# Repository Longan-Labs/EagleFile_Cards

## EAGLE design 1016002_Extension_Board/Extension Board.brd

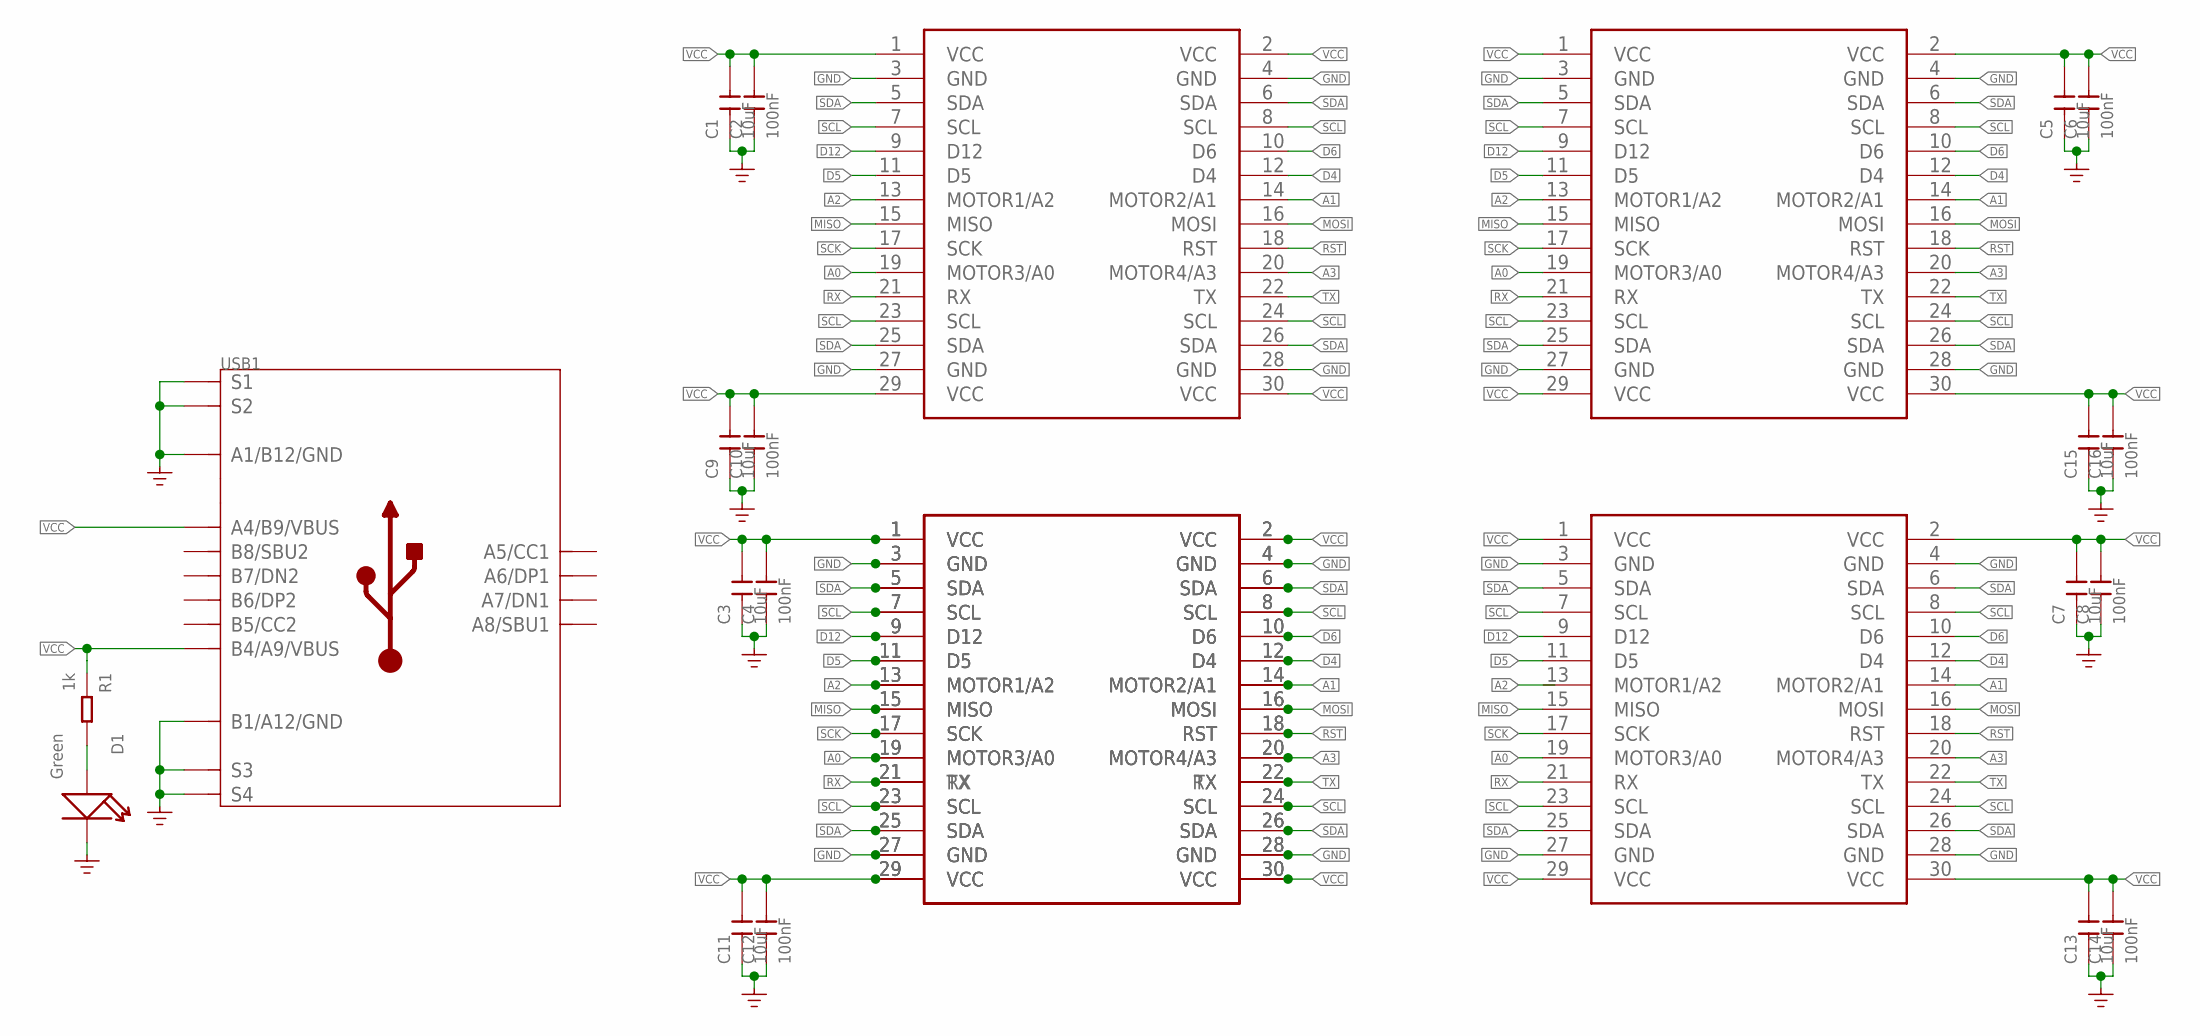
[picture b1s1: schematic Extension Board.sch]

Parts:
C1, C3, C5, C7, C9, C11, C13, C15: 10uF; C0603
C2, C4, C6, C8, C10, C12, C14, C16: 100nF; C0603
D1: Green; LED-0603
MOUDLE1, MOUDLE2, MOUDLE3: MOUDLE-2X15P-2.54'2.54'; 2X15P-2.54
MOUDLE4: MOUDLE-2X15P-2.54'90D'; 2X15P-2.54-90D
MOUDLE5: MOUDLE-2X15P-2.54-PAD'BOARD'; MOUDLE-2X15P-2.54
R1: 1k; R0603
USB1: USB2.0-TYPE-C

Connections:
A0: MOUDLE1.19 (MOTOR3/A0), MOUDLE2.19 (MOTOR3/A0), MOUDLE3.19 (MOTOR3/A0), MOUDLE4.19 (MOTOR3/A0), MOUDLE5.19 (MOTOR3/A0)
A1: MOUDLE1.14 (MOTOR2/A1), MOUDLE2.14 (MOTOR2/A1), MOUDLE3.14 (MOTOR2/A1), MOUDLE4.14 (MOTOR2/A1), MOUDLE5.14 (MOTOR2/A1)
A2: MOUDLE1.13 (MOTOR1/A2), MOUDLE2.13 (MOTOR1/A2), MOUDLE4.13 (MOTOR1/A2), MOUDLE5.13 (MOTOR1/A2)
A3: MOUDLE1.20 (MOTOR4/A3), MOUDLE2.20 (MOTOR4/A3), MOUDLE3.20 (MOTOR4/A3), MOUDLE4.20 (MOTOR4/A3), MOUDLE5.20 (MOTOR4/A3)
D4: MOUDLE1.12 (D4), MOUDLE2.12 (D4), MOUDLE3.12 (D4), MOUDLE4.12 (D4), MOUDLE5.12 (D4)
D5: MOUDLE1.11 (D5), MOUDLE2.11 (D5), MOUDLE3.11 (D5), MOUDLE4.11 (D5), MOUDLE5.11 (D5)
D6: MOUDLE1.10 (D6), MOUDLE2.10 (D6), MOUDLE3.10 (D6), MOUDLE4.10 (D6), MOUDLE5.10 (D6)
D12: MOUDLE1.9 (D12), MOUDLE2.9 (D12), MOUDLE3.9 (D12), MOUDLE4.9 (D12), MOUDLE5.9 (D12)
GND: C1.1, C2.1, C3.1, C4.1, C5.1, C6.1, C7.1, C8.1, C9.1, C10.1, C11.1, C12.1, C13.1, C14.1, C15.1, C16.1, D1.-, MOUDLE1.3 (GND), MOUDLE1.4 (GND), MOUDLE1.27 (GND), MOUDLE1.28 (GND), MOUDLE2.3 (GND), MOUDLE2.4 (GND), MOUDLE2.27 (GND), MOUDLE2.28 (GND), MOUDLE3.3 (GND), MOUDLE3.4 (GND), MOUDLE3.27 (GND), MOUDLE3.28 (GND), MOUDLE4.3 (GND), MOUDLE4.4 (GND), MOUDLE4.27 (GND), MOUDLE4.28 (GND), MOUDLE5.3 (GND), MOUDLE5.4 (GND), MOUDLE5.27 (GND), MOUDLE5.28 (GND), USB1.A1_B12 (A1/B12/GND), USB1.B1_A12 (B1/A12/GND), USB1.S1, USB1.S2, USB1.S3, USB1.S4, USB1.S5 (S1), USB1.S6 (S2)
MISO: MOUDLE1.15 (MISO), MOUDLE2.15 (MISO), MOUDLE3.15 (MISO), MOUDLE4.15 (MISO), MOUDLE5.15 (MISO)
MOSI: MOUDLE1.16 (MOSI), MOUDLE2.16 (MOSI), MOUDLE3.16 (MOSI), MOUDLE4.16 (MOSI), MOUDLE5.16 (MOSI)
unnamed: D1.+, R1.2
RST: MOUDLE1.18 (RST), MOUDLE2.18 (RST), MOUDLE3.18 (RST), MOUDLE4.18 (RST), MOUDLE5.18 (RST)
RX: MOUDLE1.21 (RX), MOUDLE2.21 (RX), MOUDLE3.21 (RX), MOUDLE4.21 (RX), MOUDLE5.21 (TX)
SCK: MOUDLE1.17 (SCK), MOUDLE2.17 (SCK), MOUDLE3.17 (SCK), MOUDLE4.17 (SCK), MOUDLE5.17 (SCK)
SCL: MOUDLE1.7 (SCL), MOUDLE1.8 (SCL), MOUDLE1.23 (SCL), MOUDLE1.24 (SCL), MOUDLE2.7 (SCL), MOUDLE2.8 (SCL), MOUDLE2.23 (SCL), MOUDLE2.24 (SCL), MOUDLE3.7 (SCL), MOUDLE3.8 (SCL), MOUDLE3.23 (SCL), MOUDLE3.24 (SCL), MOUDLE4.7 (SCL), MOUDLE4.8 (SCL), MOUDLE4.23 (SCL), MOUDLE4.24 (SCL), MOUDLE5.7 (SCL), MOUDLE5.8 (SCL), MOUDLE5.23 (SCL), MOUDLE5.24 (SCL)
SDA: MOUDLE1.5 (SDA), MOUDLE1.6 (SDA), MOUDLE1.25 (SDA), MOUDLE1.26 (SDA), MOUDLE2.5 (SDA), MOUDLE2.6 (SDA), MOUDLE2.25 (SDA), MOUDLE2.26 (SDA), MOUDLE3.5 (SDA), MOUDLE3.6 (SDA), MOUDLE3.25 (SDA), MOUDLE3.26 (SDA), MOUDLE4.5 (SDA), MOUDLE4.6 (SDA), MOUDLE4.25 (SDA), MOUDLE4.26 (SDA), MOUDLE5.5 (SDA), MOUDLE5.6 (SDA), MOUDLE5.25 (SDA), MOUDLE5.26 (SDA)
TX: MOUDLE1.22 (TX), MOUDLE2.22 (TX), MOUDLE3.22 (TX), MOUDLE4.22 (TX), MOUDLE5.22 (RX)
VCC: C1.2, C2.2, C3.2, C4.2, C5.2, C6.2, C7.2, C8.2, C9.2, C10.2, C11.2, C12.2, C13.2, C14.2, C15.2, C16.2, MOUDLE1.1 (VCC), MOUDLE1.2 (VCC), MOUDLE1.29 (VCC), MOUDLE1.30 (VCC), MOUDLE2.1 (VCC), MOUDLE2.2 (VCC), MOUDLE2.29 (VCC), MOUDLE2.30 (VCC), MOUDLE3.1 (VCC), MOUDLE3.2 (VCC), MOUDLE3.29 (VCC), MOUDLE3.30 (VCC), MOUDLE4.1 (VCC), MOUDLE4.2 (VCC), MOUDLE4.29 (VCC), MOUDLE4.30 (VCC), MOUDLE5.1 (VCC), MOUDLE5.2 (VCC), MOUDLE5.29 (VCC), MOUDLE5.30 (VCC), R1.1, USB1.A4_B9 (A4/B9/VBUS), USB1.B4_A9 (B4/A9/VBUS)

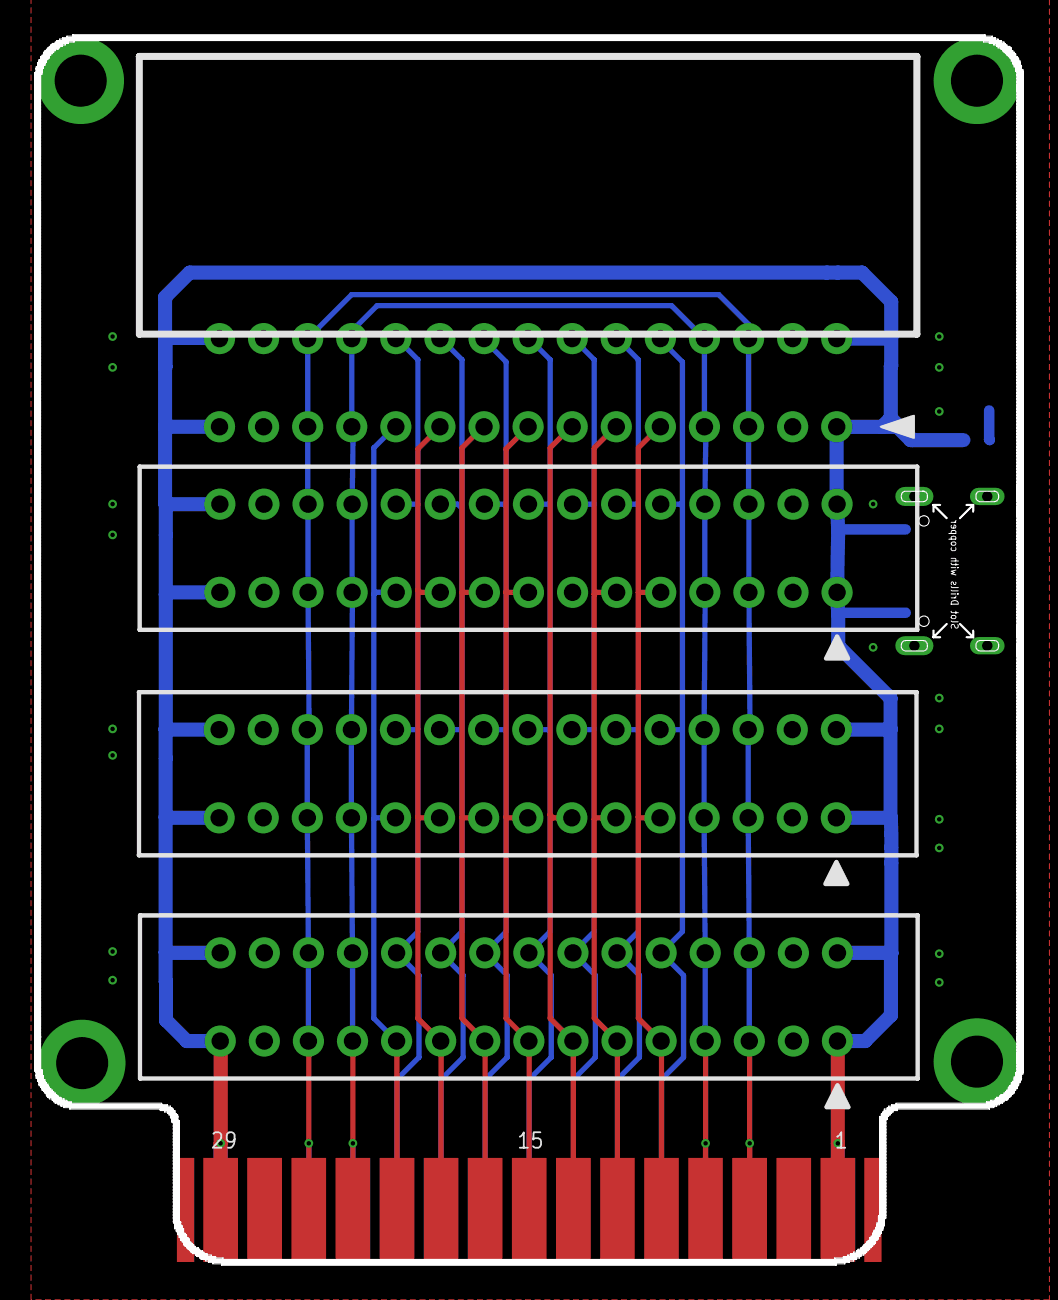
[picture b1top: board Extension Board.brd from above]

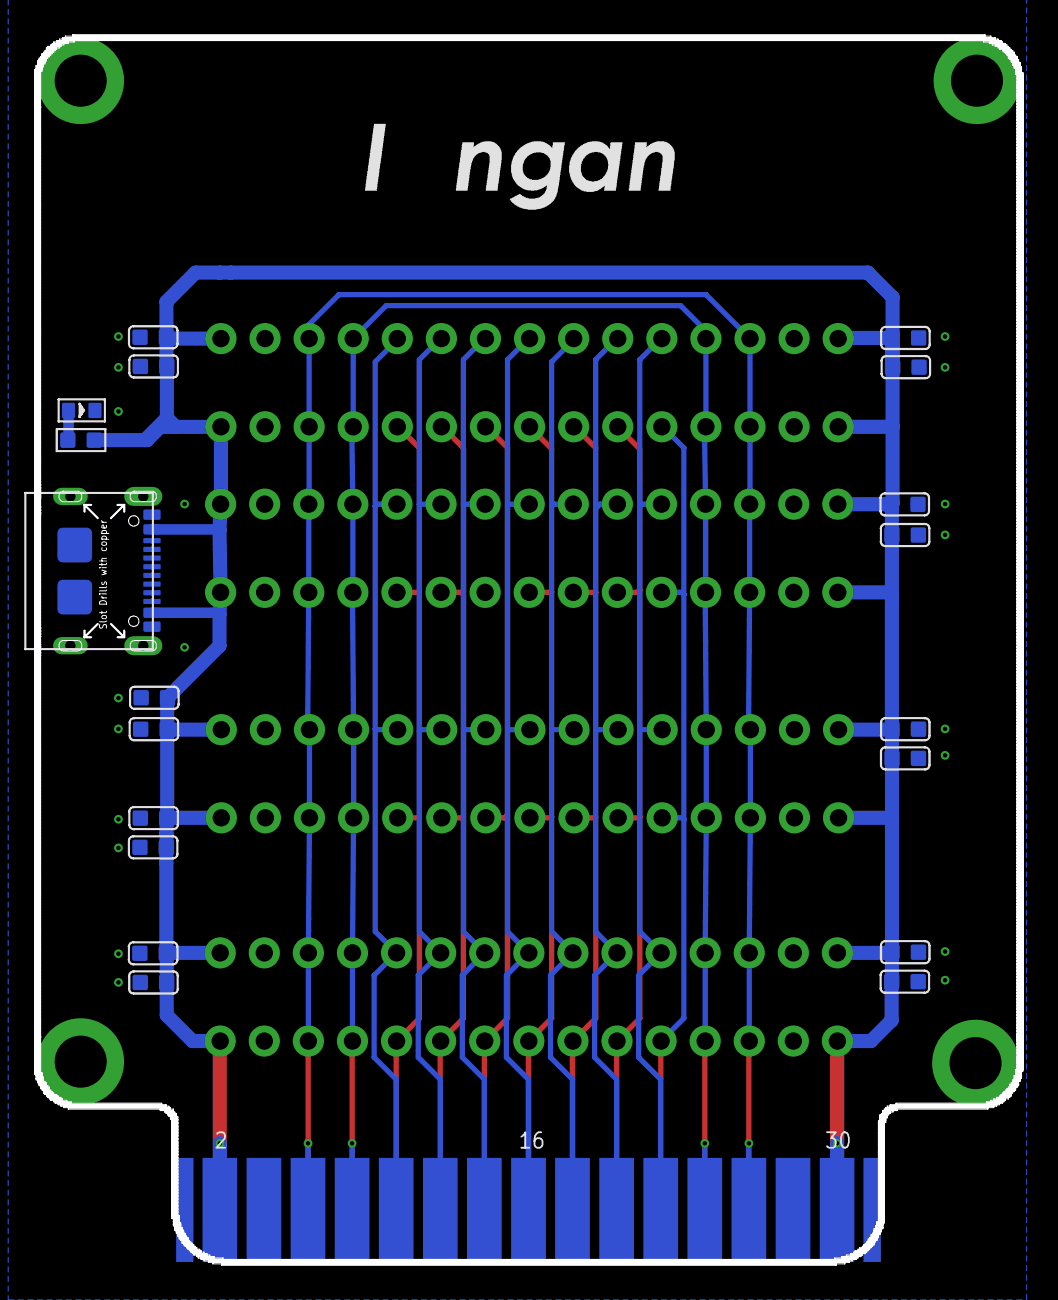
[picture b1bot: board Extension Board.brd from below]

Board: 2 copper layers, 56.9 x 70.9 mm, 25 parts (20 on the bottom side), 19 nets.

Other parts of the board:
U$3: LONGAN-COPPER-SMALL

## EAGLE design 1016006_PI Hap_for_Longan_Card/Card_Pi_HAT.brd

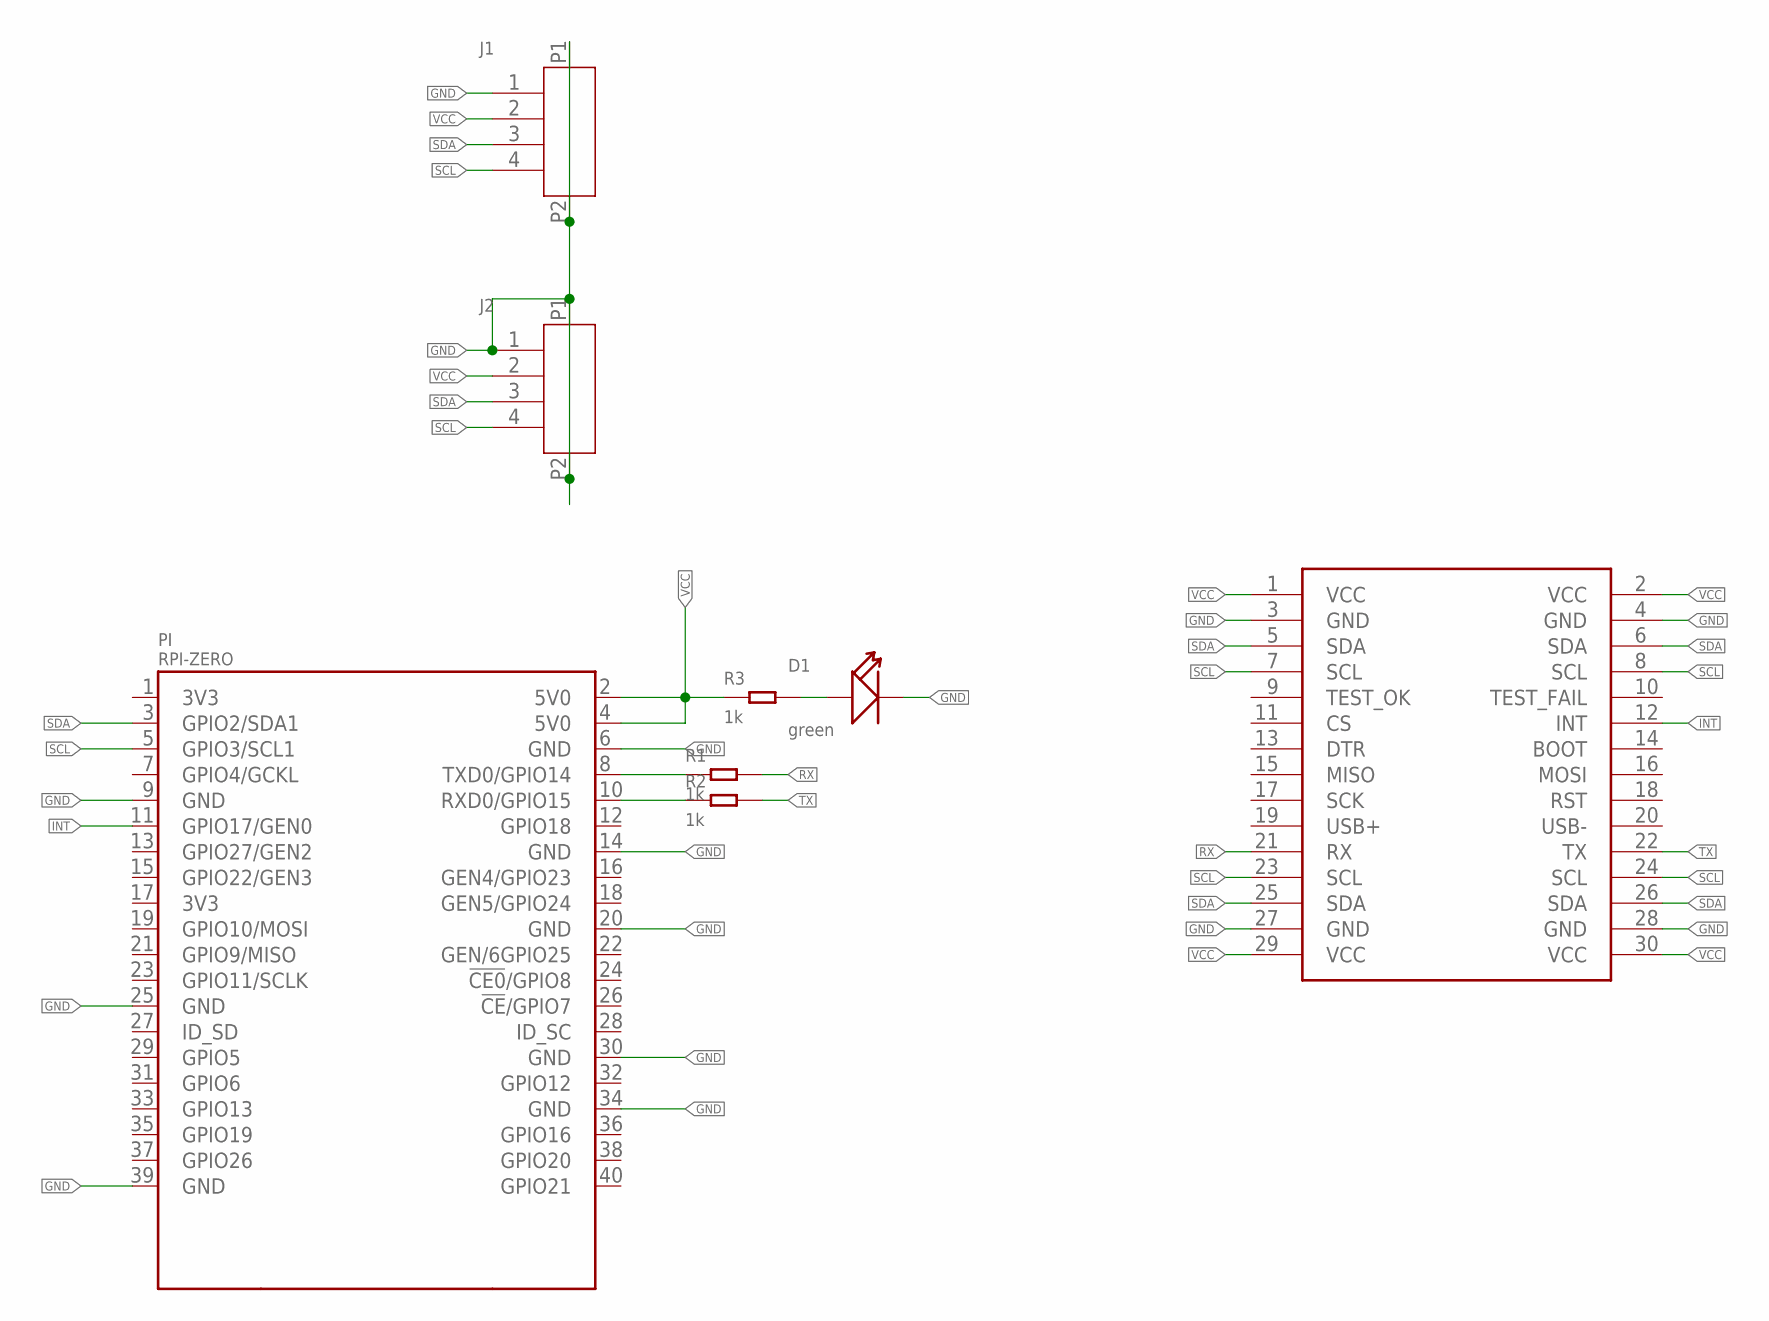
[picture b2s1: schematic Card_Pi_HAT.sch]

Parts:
D1: green; LED-0603
J1, J2: HEADER-4P-1.0; 4P-1.0-90D
MOUDLE1: MOUDLE-2X15P-2.54'90D'; 2X15P-2.54-90D
PI: RPI-ZERO; RASPBERRYPI_BASTELSTUBE_V13_RASPI_BOARD_B+_FULL
R1, R2, R3: 1k; R0603

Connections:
GND: D1.-, J1.1, J1.P1, J1.P2, J2.1, J2.P1, J2.P2, MOUDLE1.3 (GND), MOUDLE1.4 (GND), MOUDLE1.27 (GND), MOUDLE1.28 (GND), PI.6 (GND), PI.9 (GND), PI.14 (GND), PI.20 (GND), PI.25 (GND), PI.30 (GND), PI.34 (GND), PI.39 (GND)
INT: MOUDLE1.12 (INT), PI.11 (GPIO17/GEN0)
unnamed: PI.8 (TXD0/GPIO14), R1.1
unnamed: PI.10 (RXD0/GPIO15), R2.1
unnamed: D1.+, R3.2
RX: MOUDLE1.21 (RX), R1.2
SCL: J1.4, J2.4, MOUDLE1.7 (SCL), MOUDLE1.8 (SCL), MOUDLE1.23 (SCL), MOUDLE1.24 (SCL), PI.5 (GPIO3/SCL1)
SDA: J1.3, J2.3, MOUDLE1.5 (SDA), MOUDLE1.6 (SDA), MOUDLE1.25 (SDA), MOUDLE1.26 (SDA), PI.3 (GPIO2/SDA1)
TX: MOUDLE1.22 (TX), R2.2
VCC: J1.2, J2.2, MOUDLE1.1 (VCC), MOUDLE1.2 (VCC), MOUDLE1.29 (VCC), MOUDLE1.30 (VCC), PI.2 (5V0), PI.4 (5V0), R3.1

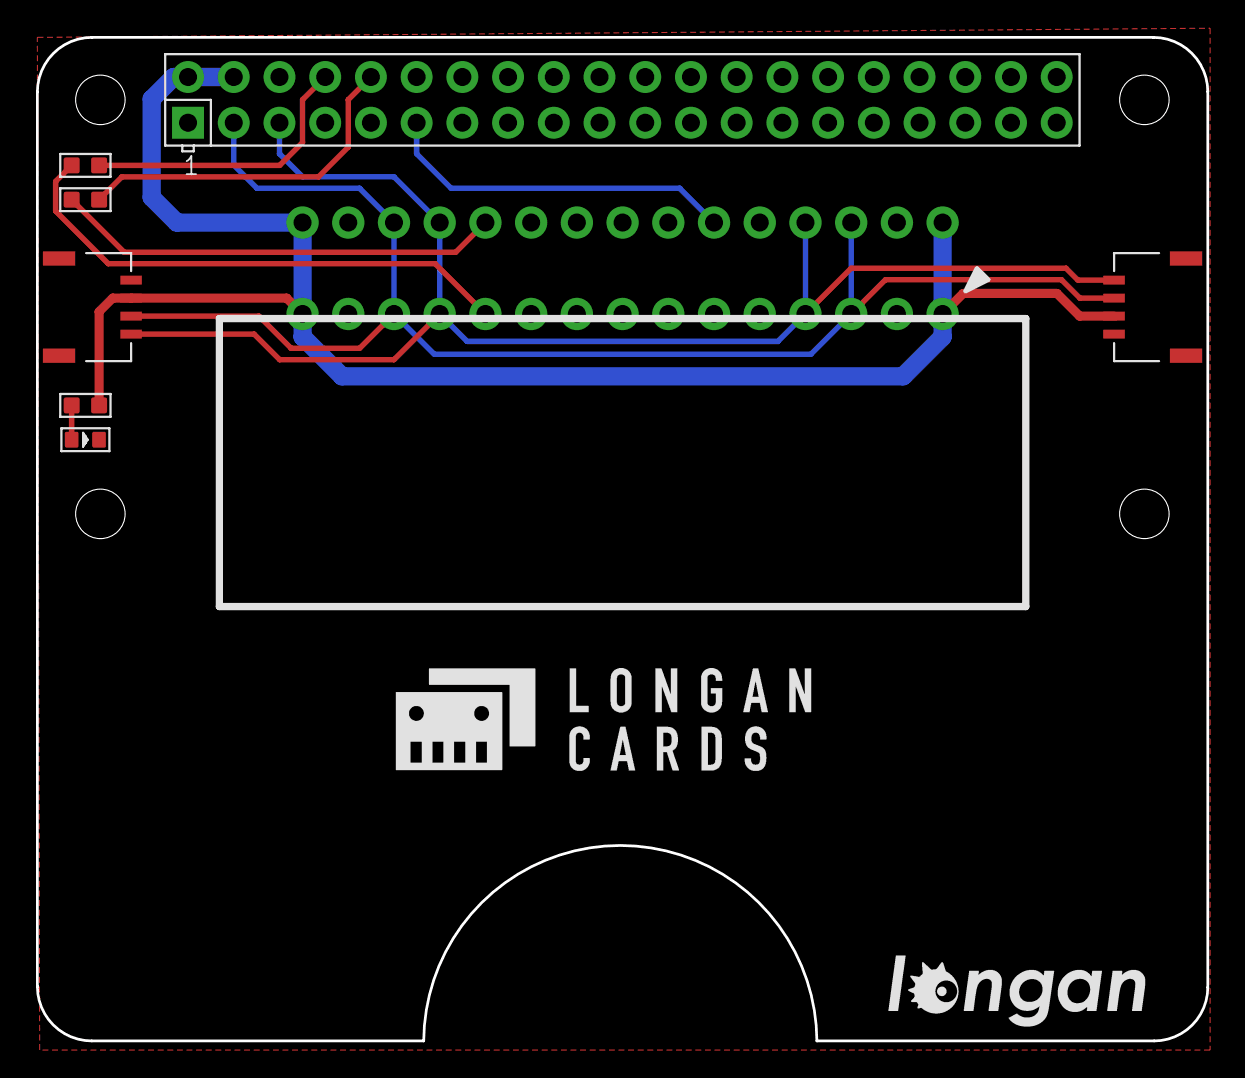
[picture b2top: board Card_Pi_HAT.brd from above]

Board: 2 copper layers, 65.0 x 55.8 mm, 11 parts (1 on the bottom side), 10 nets.

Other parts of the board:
U$2: LONGAN-CARDS-BIG
U$3: LONGAN-SILK-SMALLER
U$4: LONGAN-CARDS-MIDDLE

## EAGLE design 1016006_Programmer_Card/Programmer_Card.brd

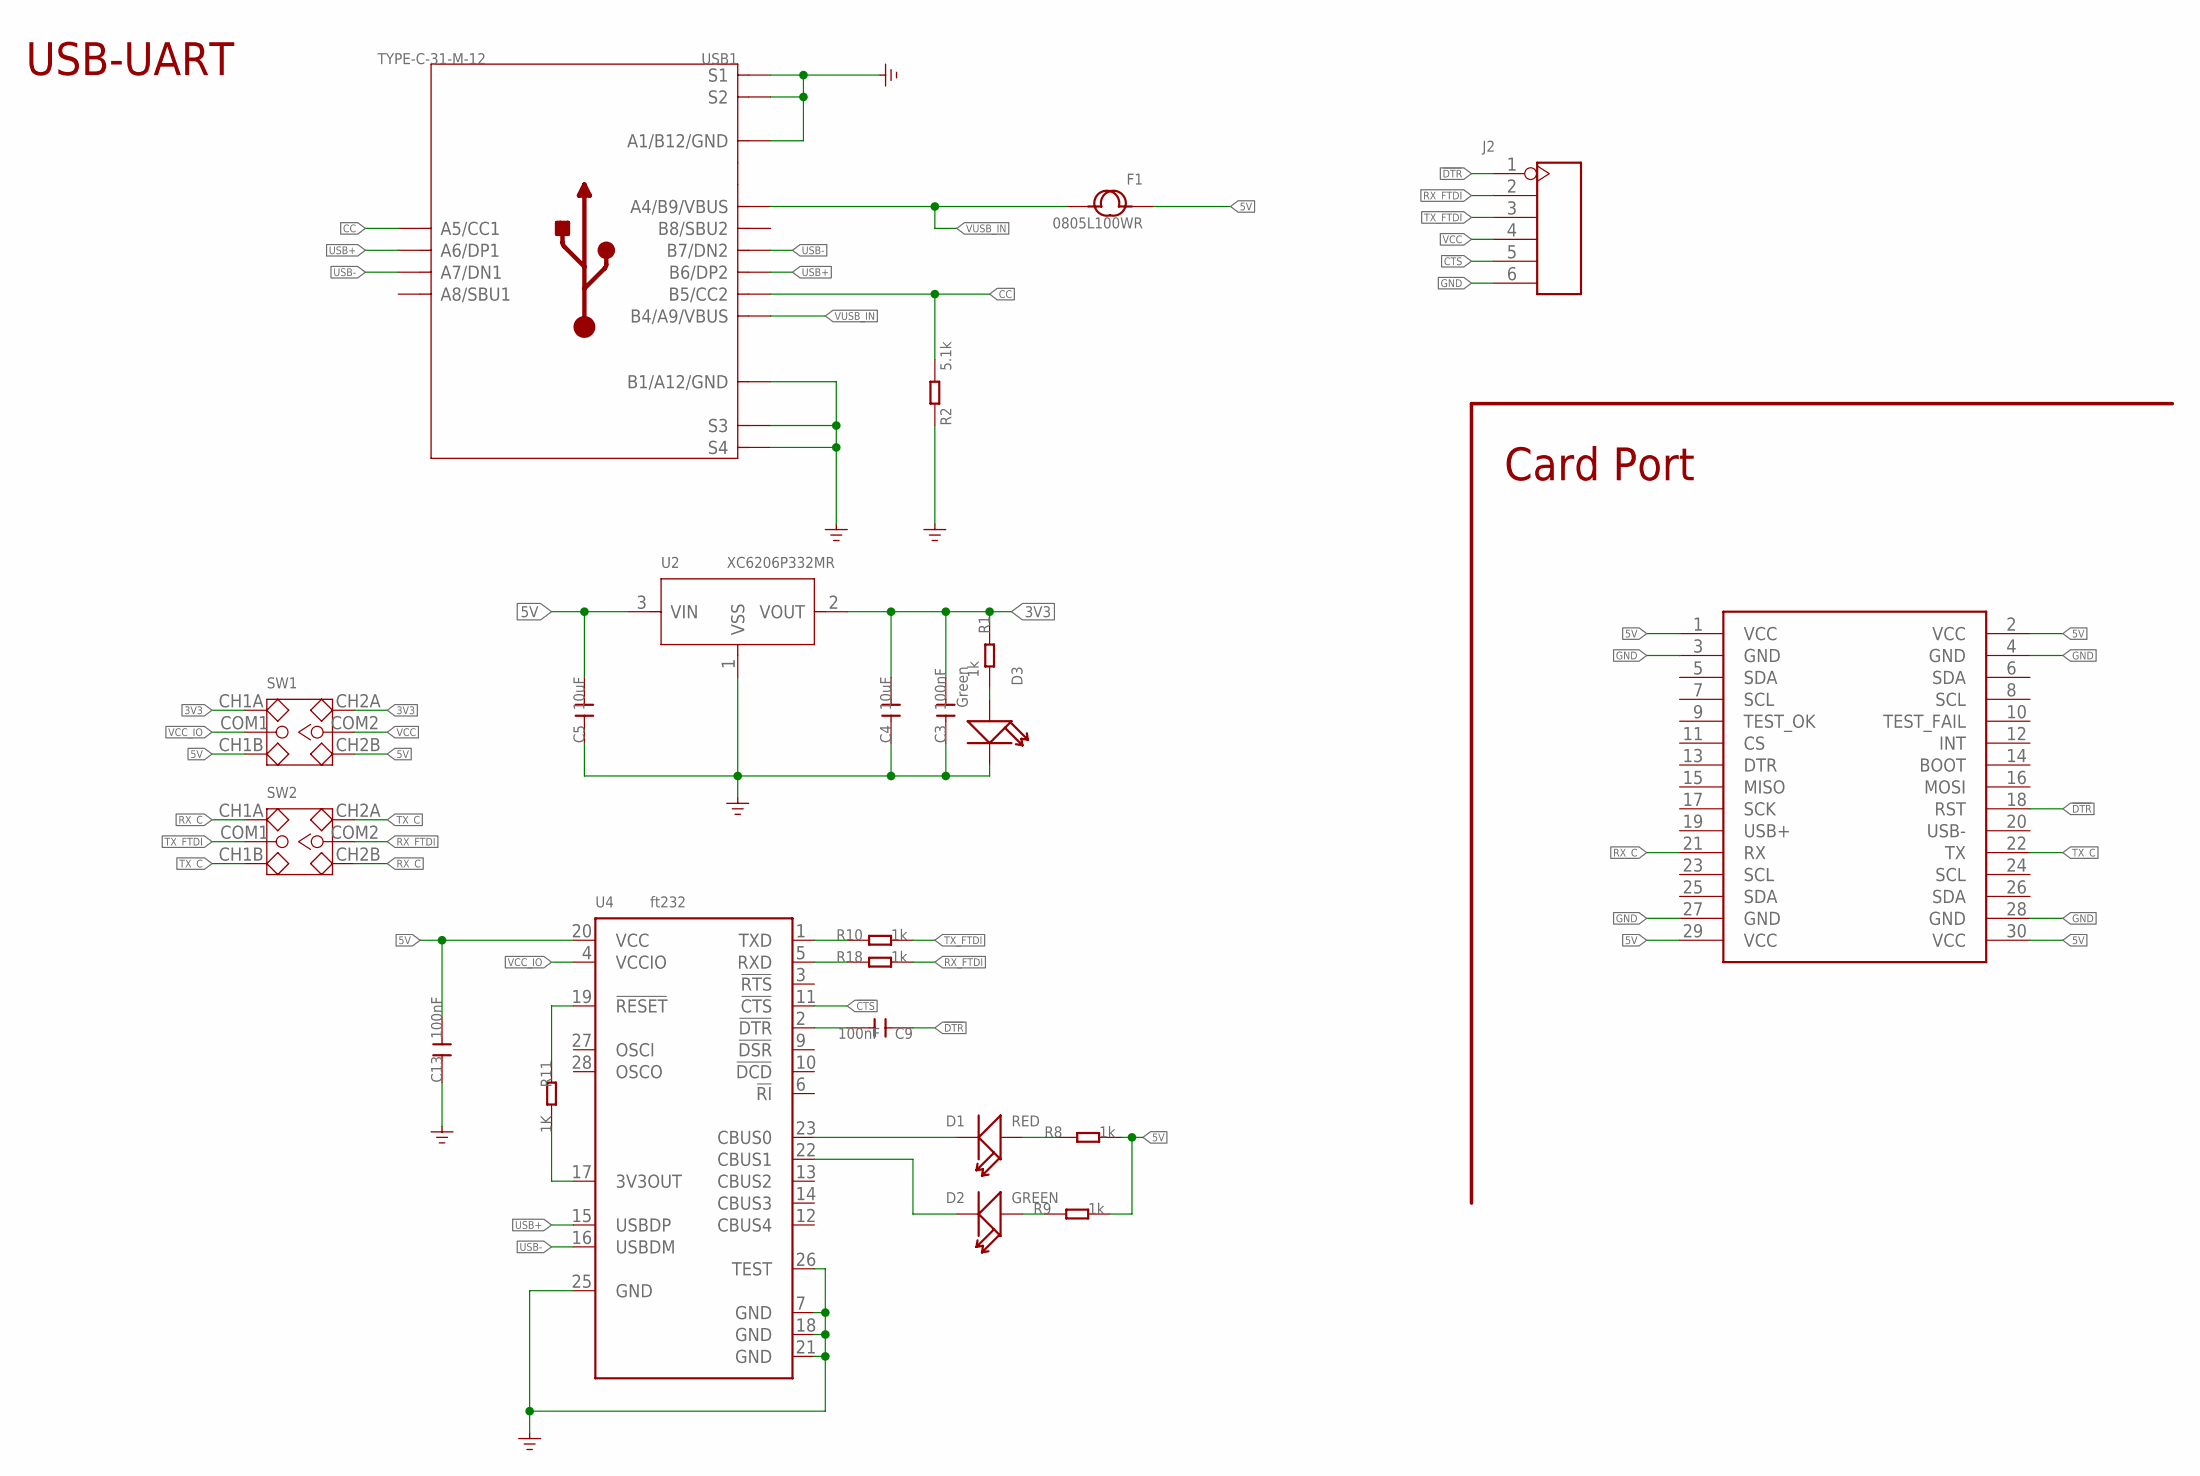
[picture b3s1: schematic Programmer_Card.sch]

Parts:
C3, C9, C13: 100nF; C0603
C4, C5: 10uF; C0603
D1: RED; LED-0603
D2: GREEN; LED-0603
D3: Green; LED-0603
F1: 0805L100WR; F0805
J2: HEADER-6P-65/35MIL; H6-2.54-C65D35MIL
MOUDLE1: MOUDLE-2X15P-2.54'BOARD'; MOUDLE-2X15P-2.54
R1, R8, R9, R10, R18: 1k; R0603
R2: 5.1k; R0603
R11: 1K; R0603
SW1, SW2: SWITCH-2CH-6P; SW6-2.5-SMD-9.2X3.5X3.5MM
U2: XC6206P332MR; SOT-23
U4: ft232; SSOP28-0.65-10.2X5.2MM
USB1: TYPE-C-31-M-12; USB2.0-TYPE-C

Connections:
3V3: C3.2, C4.2, R1.1, SW1.CH1A, SW1.CH2A, U2.2 (VOUT)
5V: C5.2, C13.1, F1.1, MOUDLE1.1 (VCC), MOUDLE1.2 (VCC), MOUDLE1.29 (VCC), MOUDLE1.30 (VCC), R8.2, R9.2, SW1.CH1B, SW1.CH2B, U2.3 (VIN), U4.20 (VCC)
!CTS: J2.5, U4.11 (!CTS)
!DTR: C9.1, J2.1, MOUDLE1.18 (RST)
CC: R2.2, USB1.A5 (A5/CC1), USB1.B5 (B5/CC2)
GND: C3.1, C4.1, C5.1, C13.2, D3.-, J2.6, MOUDLE1.3 (GND), MOUDLE1.4 (GND), MOUDLE1.27 (GND), MOUDLE1.28 (GND), R2.1, U2.1 (VSS), U4.7 (GND), U4.18 (GND), U4.21 (GND), U4.25 (GND), U4.26 (TEST), USB1.A1_B12 (A1/B12/GND), USB1.B1_A12 (B1/A12/GND), USB1.S1, USB1.S2, USB1.S3, USB1.S4, USB1.S5 (S1), USB1.S6 (S2)
unnamed: R11.2, U4.17 (3V3OUT)
unnamed: D3.+, R1.2
unnamed: R11.1, U4.19 (!RESET)
unnamed: R10.1, U4.1 (TXD)
unnamed: D1.-, U4.23 (CBUS0)
unnamed: D2.-, U4.22 (CBUS1)
unnamed: D1.+, R8.1
unnamed: D2.+, R9.1
unnamed: R18.1, U4.5 (RXD)
unnamed: C9.2, U4.2 (!DTR)
RX_C: MOUDLE1.21 (RX), SW2.CH1A, SW2.CH2B
RX_FTDI: J2.2, R18.2, SW2.COM2
TX_C: MOUDLE1.22 (TX), SW2.CH1B, SW2.CH2A
TX_FTDI: J2.3, R10.2, SW2.COM1
USB+: U4.15 (USBDP), USB1.A6 (A6/DP1), USB1.B6 (B6/DP2)
USB-: U4.16 (USBDM), USB1.A7 (A7/DN1), USB1.B7 (B7/DN2)
VCC: J2.4, SW1.COM2
VCC_IO: SW1.COM1, U4.4 (VCCIO)
VUSB_IN: F1.2, USB1.A4_B9 (A4/B9/VBUS), USB1.B4_A9 (B4/A9/VBUS)

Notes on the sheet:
USB-UART
Card Port

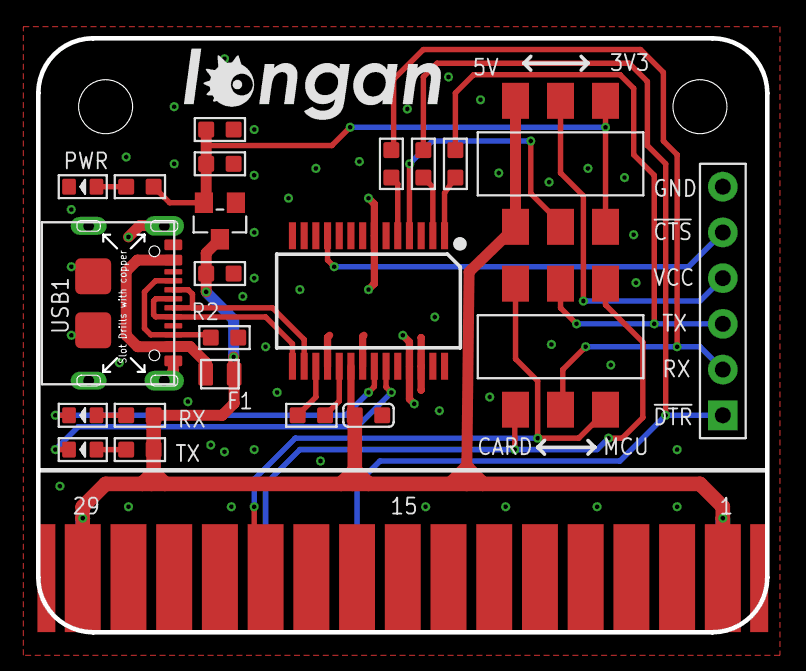
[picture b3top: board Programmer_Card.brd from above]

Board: 2 copper layers, 40.5 x 33.0 mm, 25 parts (1 on the bottom side), 25 nets.

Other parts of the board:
U$1: LONGAN-SILK-SMALLER
U$6: LONGAN-CARDS-MIDDLE

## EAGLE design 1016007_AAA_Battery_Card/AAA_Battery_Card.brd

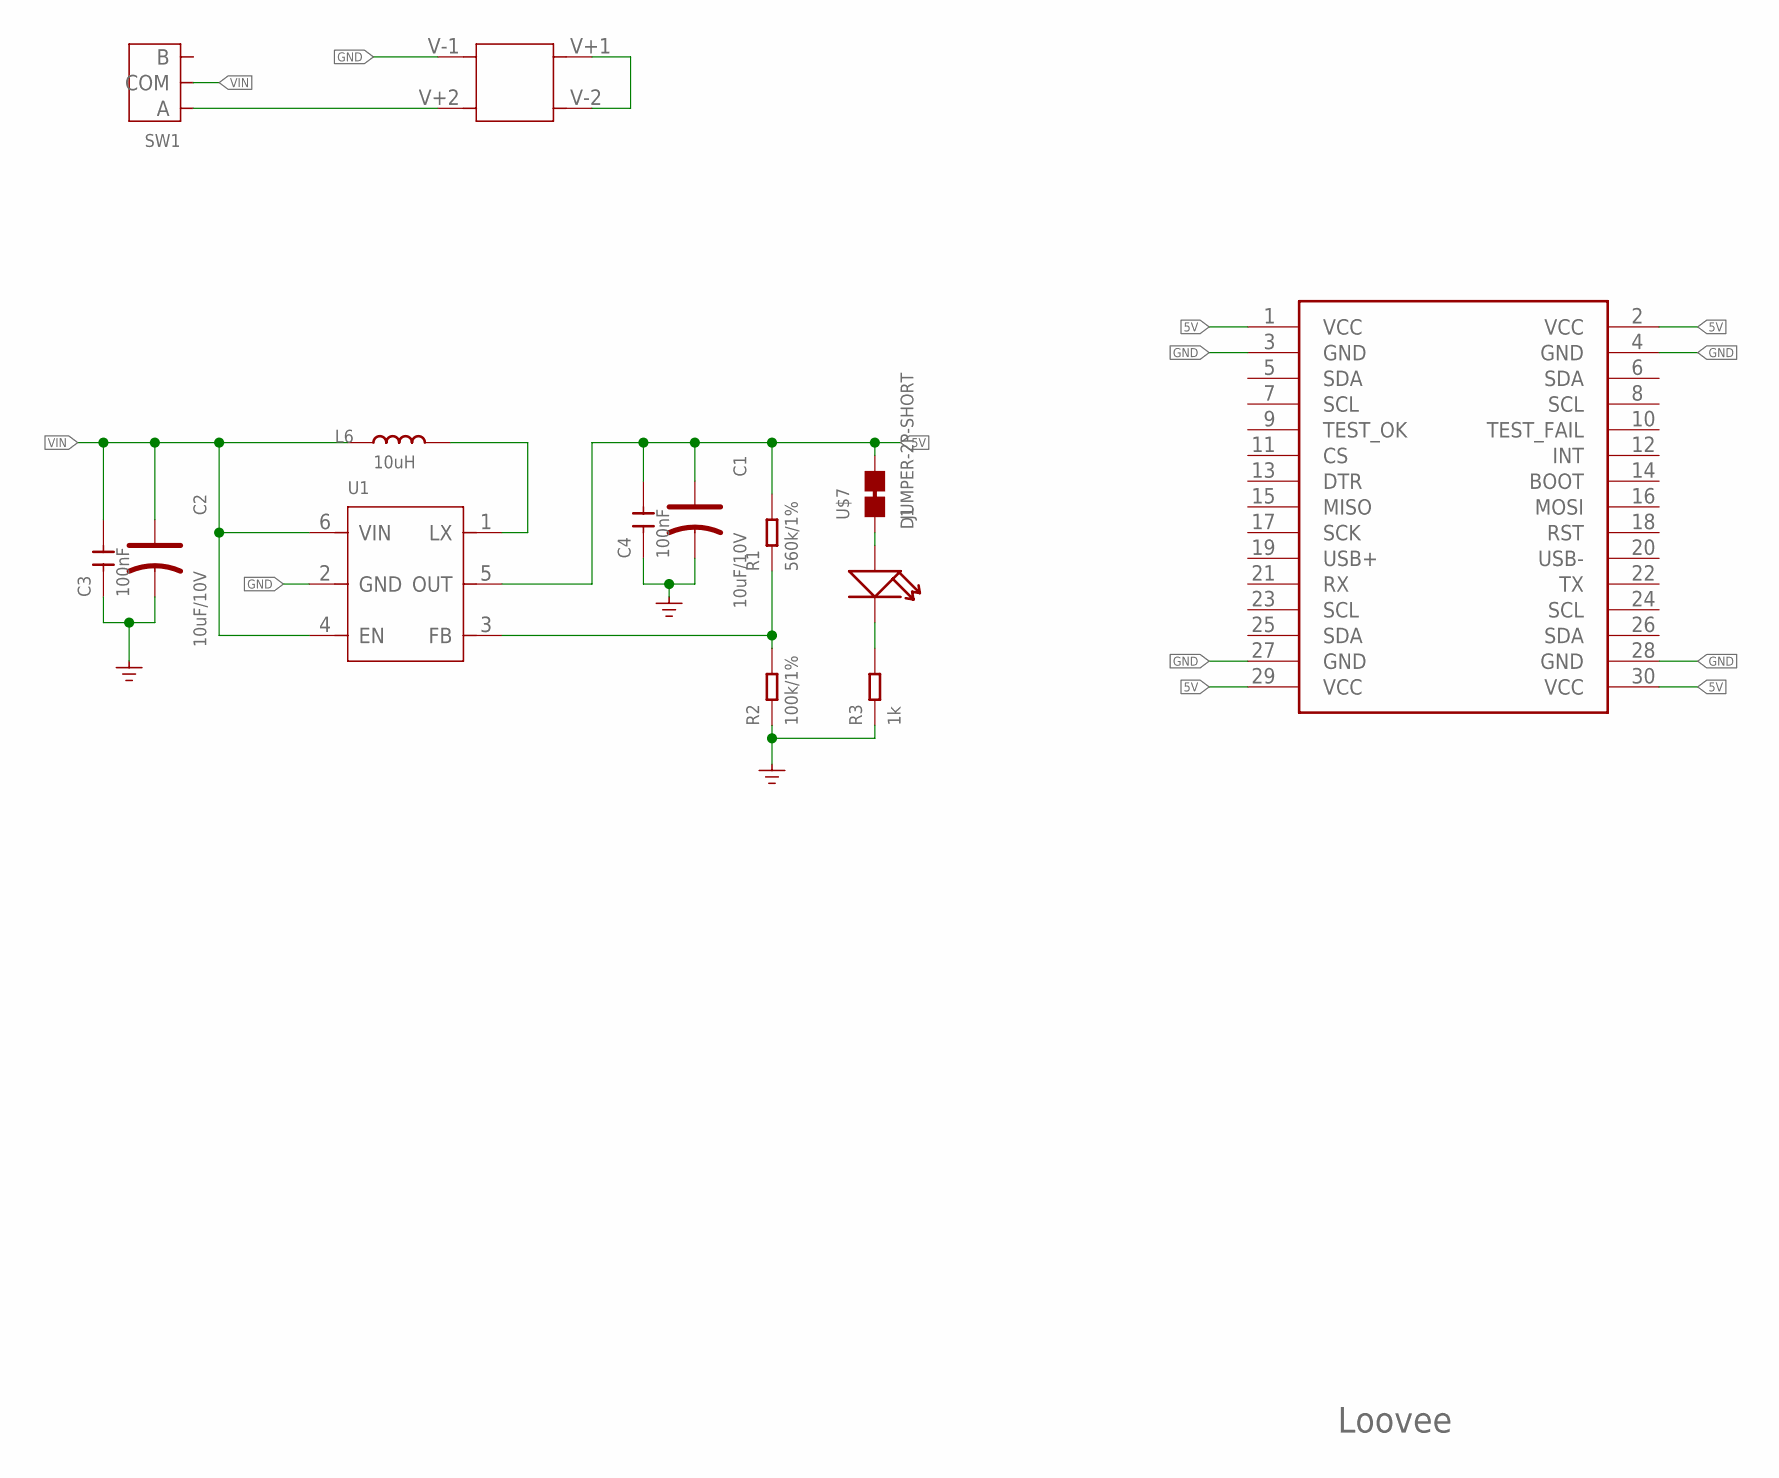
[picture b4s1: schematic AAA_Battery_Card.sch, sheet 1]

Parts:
BAT1: BAT-1.5VX2-HOLDER; BAT-SMD-54.6X22.4MM
C1, C2: 10uF/10V; AVX-B
C3, C4: 100nF; C0603
D1: LED'0603'; LED-0603
L6: 10uH; L0420
MOUDLE1: MOUDLE-2X15P-2.54'BOARD'; MOUDLE-2X15P-2.54
R1: 560k/1%; R0603
R2: 100k/1%; R0603
R3: 1k; R0603
SW1: SWITCH-2H-3P; SW3-2.5-9X3.5MM
U1: PMIC-PS7516; SOT-23-6
U$7: JUMPER-2P-SHORT; 2P-SMD-SHORT

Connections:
5V: C1.+, C4.2, MOUDLE1.1 (VCC), MOUDLE1.2 (VCC), MOUDLE1.29 (VCC), MOUDLE1.30 (VCC), R1.2, U1.5 (OUT), U$7.2
GND: BAT1.V-1 (1), C1.-, C2.-, C3.1, C4.1, MOUDLE1.3 (GND), MOUDLE1.4 (GND), MOUDLE1.27 (GND), MOUDLE1.28 (GND), R2.1, R3.1, U1.2 (GND)
unnamed: BAT1.V+2 (3), SW1.1 (A)
unnamed: BAT1.V+1 (2), BAT1.V-2 (4)
unnamed: D1.-, R3.2
unnamed: L6.2, U1.1 (LX)
unnamed: D1.+, U$7.1
unnamed: R1.1, R2.2, U1.3 (FB)
VIN: C2.+, C3.2, L6.1, SW1.2 (COM), U1.4 (EN), U1.6 (VIN)

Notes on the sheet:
Loovee

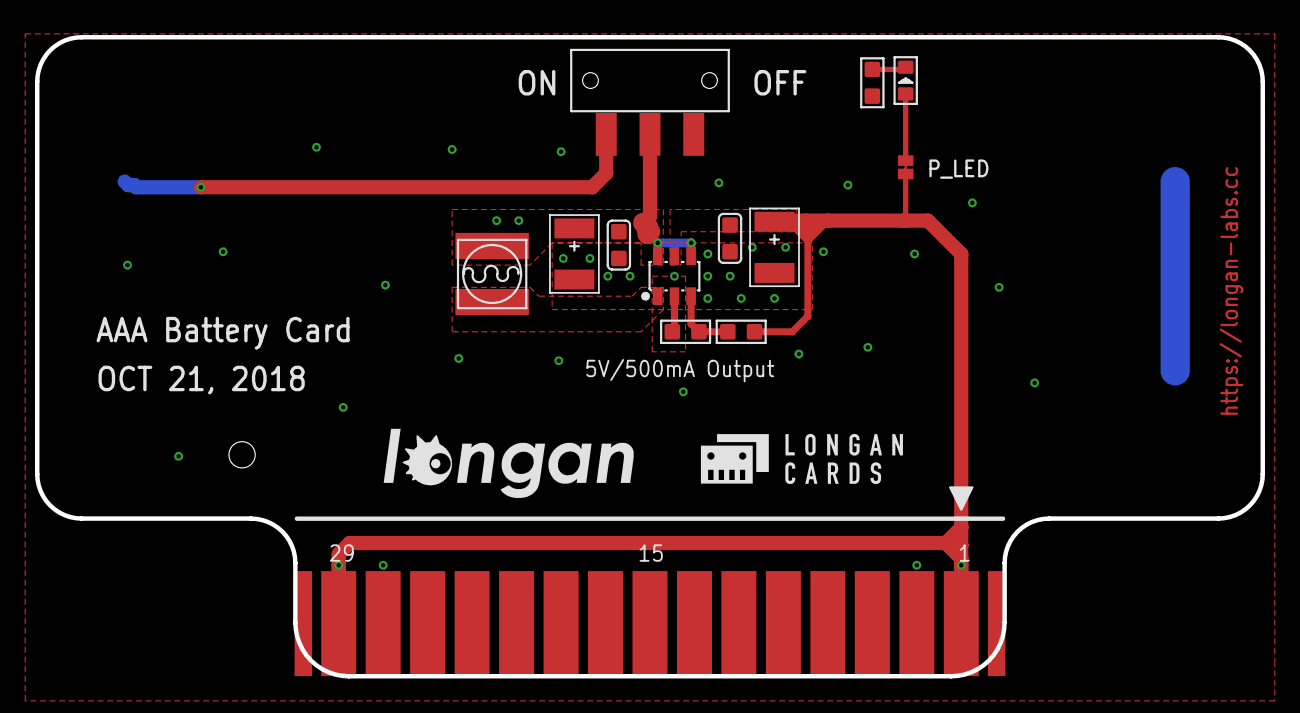
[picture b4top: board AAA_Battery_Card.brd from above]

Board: 2 copper layers, 70.0 x 36.5 mm, 16 parts (1 on the bottom side), 9 nets.

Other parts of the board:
U$1: LONGAN-CARDS-SMALL
U$6: LONGAN-SILK-SMALLER
